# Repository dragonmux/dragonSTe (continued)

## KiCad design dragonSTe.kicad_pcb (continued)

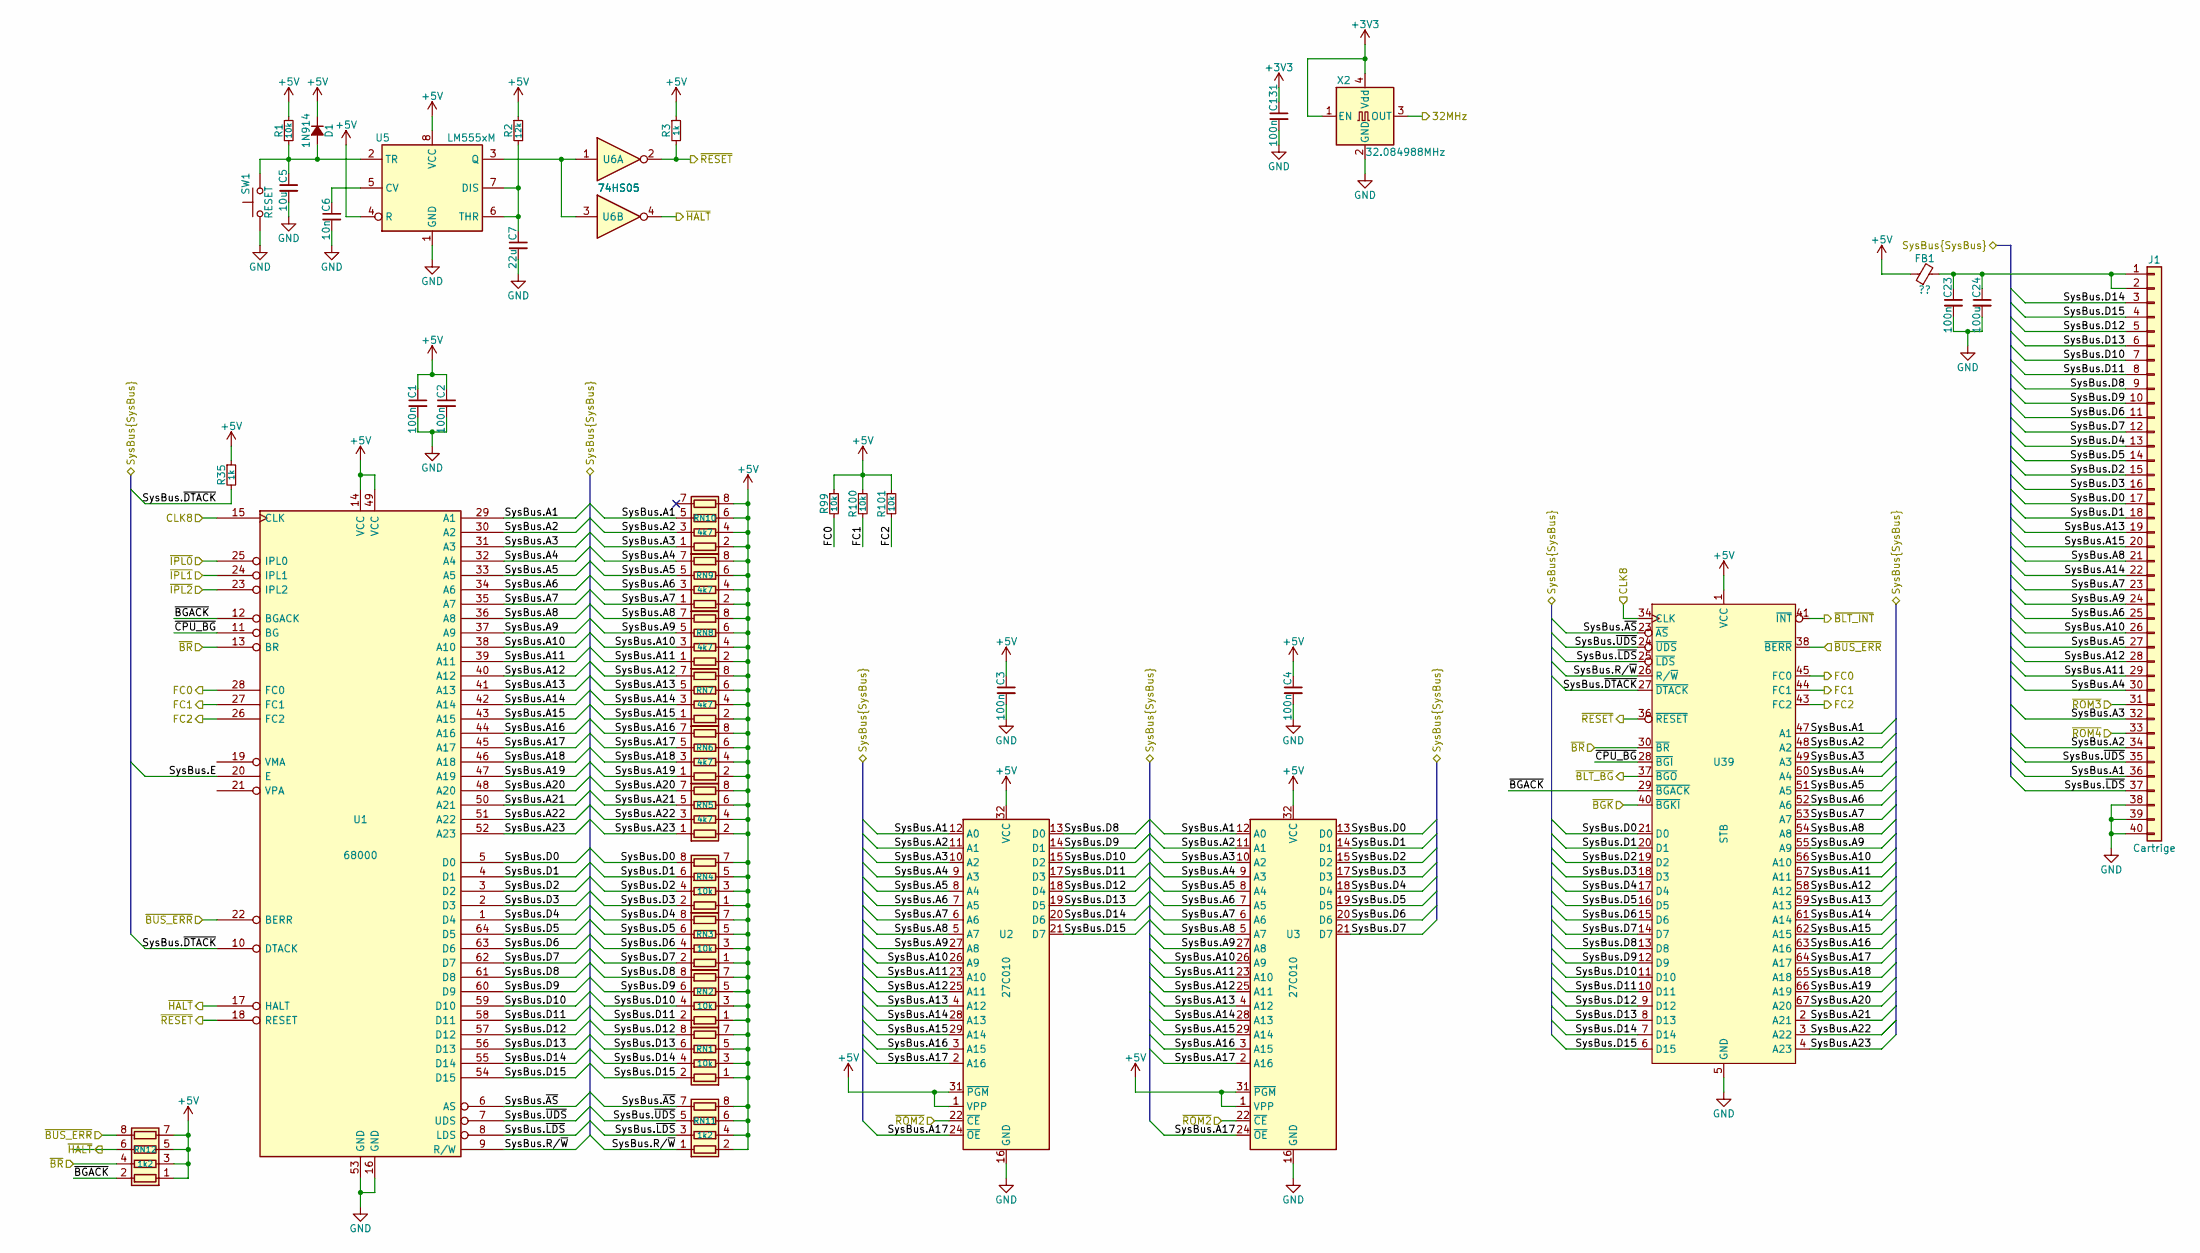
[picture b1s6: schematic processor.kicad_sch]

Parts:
C1, C2, C3, C4, C23, C131: 100n; C0603
C5: 10u; C0603
C6: 10n; C0603
C7: 22u; C0603
C24: 100u; C0603
D1: 1N914; D_SOD-323F; MPN 1N914BWS
FB1: ??
J1: Cartrige
R1, R99, R100, R101: 10k; R0603
R2: 12k; R0603
R3, R35: 1k; R0603
RN1, RN2, RN3, RN4: 10k; R0603_Array_Concave_4
RN5, RN6, RN7, RN8, RN9, RN10: 4k7; R0603_Array_Concave_4
RN11, RN12: 1k2; R0603_Array_Concave_4
SW1: RESET; B3U-1000P-B
U1: 68000; DIP-64_W22.86mm_Socket
U2, U3: 27C010; DIP-32_W15.24mm_Socket; MPN 4832-6000-CP
U5: LM555xM; SO-8_3.9x4.9mm_P1.27mm
U6: 74HS05; SO-14_3.9x8.65mm_P1.27mm; MPN SN74HC05DR
U39: STB; PLCC-68_SMD-Socket; MPN MC-68PLCC-SMT
X2: 32.084988MHz; SMD3225; MPN DSC8004CI2

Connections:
+3V3: C131.1, X2.1 (EN), X2.4 (Vdd); also elsewhere on the board
+5V: C1.1, C2.1, C3.1, C4.1, D1.1 (K), FB1.1, R1.1, R2.1, R3.1, R35.1, R99.1, R100.1, R101.1, RN1.1 (R1.1), RN1.3 (R3.1), RN1.5 (R4.2), RN1.7 (R2.2), RN2.1 (R1.1), RN2.3 (R3.1), RN2.5 (R4.2), RN2.7 (R2.2), RN3.1 (R1.1), RN3.3 (R3.1), RN3.5 (R4.2), RN3.7 (R2.2), RN4.1 (R1.1), RN4.3 (R3.1), RN4.5 (R4.2), RN4.7 (R2.2), RN5.2 (R2.1), RN5.4 (R4.1), RN5.6 (R3.2), RN5.8 (R1.2), RN6.2 (R2.1), RN6.4 (R4.1), RN6.6 (R3.2), RN6.8 (R1.2), RN7.2 (R2.1), RN7.4 (R4.1), RN7.6 (R3.2), RN7.8 (R1.2), RN8.2 (R2.1), RN8.4 (R4.1), RN8.6 (R3.2), RN8.8 (R1.2), RN9.2 (R2.1), RN9.4 (R4.1), RN9.6 (R3.2), RN9.8 (R1.2), RN10.2 (R2.1), RN10.4 (R4.1), RN10.6 (R3.2), RN10.8 (R1.2), RN11.2 (R2.1), RN11.4 (R4.1), RN11.6 (R3.2), RN11.8 (R1.2), RN12.1 (R1.1), RN12.3 (R3.1), RN12.5 (R4.2), RN12.7 (R2.2), U1.14 (VCC), U1.49 (VCC), U2.1 (VPP), U2.31 (~PGM), U2.32 (VCC), U3.1 (VPP), U3.31 (~PGM), U3.32 (VCC), U5.4 (R), U5.8 (VCC), U39.1 (VCC), U39.33 (VCC); also elsewhere on the board
/CPU+ROMs/32MHz: X2.3 (OUT); also elsewhere on the board
/CPU+ROMs/CLK8: U1.15 (CLK), U39.34 (CLK); also elsewhere on the board
/CPU+ROMs/FC0: R99.2, U1.28 (FC0), U39.45 (FC0); also elsewhere on the board
/CPU+ROMs/FC1: R100.2, U1.27 (FC1), U39.44 (FC1); also elsewhere on the board
/CPU+ROMs/FC2: R101.2, U1.26 (FC2), U39.43 (FC2); also elsewhere on the board
/CPU+ROMs/SysBus.A1: J1.36, RN10.5 (R4.2), U1.29 (A1), U2.12 (A0), U3.12 (A0), U39.47 (A1); also elsewhere on the board
/CPU+ROMs/SysBus.A2: J1.34, RN10.3 (R3.1), U1.30 (A2), U2.11 (A1), U3.11 (A1), U39.48 (A2); also elsewhere on the board
/CPU+ROMs/SysBus.A3: J1.32, RN10.1 (R1.1), U1.31 (A3), U2.10 (A2), U3.10 (A2), U39.49 (A3); also elsewhere on the board
/CPU+ROMs/SysBus.A4: J1.30, RN9.7 (R2.2), U1.32 (A4), U2.9 (A3), U3.9 (A3), U39.50 (A4); also elsewhere on the board
/CPU+ROMs/SysBus.A5: J1.27, RN9.5 (R4.2), U1.33 (A5), U2.8 (A4), U3.8 (A4), U39.51 (A5); also elsewhere on the board
/CPU+ROMs/SysBus.A6: J1.25, RN9.3 (R3.1), U1.34 (A6), U2.7 (A5), U3.7 (A5), U39.52 (A6); also elsewhere on the board
/CPU+ROMs/SysBus.A7: J1.23, RN9.1 (R1.1), U1.35 (A7), U2.6 (A6), U3.6 (A6), U39.53 (A7); also elsewhere on the board
/CPU+ROMs/SysBus.A8: J1.21, RN8.7 (R2.2), U1.36 (A8), U2.5 (A7), U3.5 (A7), U39.54 (A8); also elsewhere on the board
/CPU+ROMs/SysBus.A9: J1.24, RN8.5 (R4.2), U1.37 (A9), U2.27 (A8), U3.27 (A8), U39.55 (A9); also elsewhere on the board
/CPU+ROMs/SysBus.A10: J1.26, RN8.3 (R3.1), U1.38 (A10), U2.26 (A9), U3.26 (A9), U39.56 (A10); also elsewhere on the board
/CPU+ROMs/SysBus.A11: J1.29, RN8.1 (R1.1), U1.39 (A11), U2.23 (A10), U3.23 (A10), U39.57 (A11); also elsewhere on the board
/CPU+ROMs/SysBus.A12: J1.28, RN7.7 (R2.2), U1.40 (A12), U2.25 (A11), U3.25 (A11), U39.58 (A12); also elsewhere on the board
/CPU+ROMs/SysBus.A13: J1.19, RN7.5 (R4.2), U1.41 (A13), U2.4 (A12), U3.4 (A12), U39.59 (A13); also elsewhere on the board
/CPU+ROMs/SysBus.A14: J1.22, RN7.3 (R3.1), U1.42 (A14), U2.28 (A13), U3.28 (A13), U39.61 (A14); also elsewhere on the board
/CPU+ROMs/SysBus.A15: J1.20, RN7.1 (R1.1), U1.43 (A15), U2.29 (A14), U3.29 (A14), U39.62 (A15); also elsewhere on the board
/CPU+ROMs/SysBus.A16: RN6.7 (R2.2), U1.44 (A16), U2.3 (A15), U3.3 (A15), U39.63 (A16); also elsewhere on the board
/CPU+ROMs/SysBus.A17: RN6.5 (R4.2), U1.45 (A17), U2.2 (A16), U2.24 (~OE), U3.2 (A16), U3.24 (~OE), U39.64 (A17); also elsewhere on the board
/CPU+ROMs/SysBus.A18: RN6.3 (R3.1), U1.46 (A18), U39.65 (A18); also elsewhere on the board
/CPU+ROMs/SysBus.A19: RN6.1 (R1.1), U1.47 (A19), U39.66 (A19); also elsewhere on the board
/CPU+ROMs/SysBus.A20: RN5.7 (R2.2), U1.48 (A20), U39.67 (A20); also elsewhere on the board
/CPU+ROMs/SysBus.A21: RN5.5 (R4.2), U1.50 (A21), U39.2 (A21); also elsewhere on the board
/CPU+ROMs/SysBus.A22: RN5.3 (R3.1), U1.51 (A22), U39.3 (A22); also elsewhere on the board
/CPU+ROMs/SysBus.A23: RN5.1 (R1.1), U1.52 (A23), U39.4 (A23); also elsewhere on the board
/CPU+ROMs/SysBus.D0: J1.17, RN4.8 (R1.2), U1.5 (D0), U3.13 (D0), U39.21 (D0); also elsewhere on the board
/CPU+ROMs/SysBus.D1: J1.18, RN4.6 (R3.2), U1.4 (D1), U3.14 (D1), U39.20 (D1); also elsewhere on the board
/CPU+ROMs/SysBus.D2: J1.15, RN4.4 (R4.1), U1.3 (D2), U3.15 (D2), U39.19 (D2); also elsewhere on the board
/CPU+ROMs/SysBus.D3: J1.16, RN4.2 (R2.1), U1.2 (D3), U3.17 (D3), U39.18 (D3); also elsewhere on the board
/CPU+ROMs/SysBus.D4: J1.13, RN3.8 (R1.2), U1.1 (D4), U3.18 (D4), U39.17 (D4); also elsewhere on the board
/CPU+ROMs/SysBus.D5: J1.14, RN3.6 (R3.2), U1.64 (D5), U3.19 (D5), U39.16 (D5); also elsewhere on the board
/CPU+ROMs/SysBus.D6: J1.11, RN3.4 (R4.1), U1.63 (D6), U3.20 (D6), U39.15 (D6); also elsewhere on the board
/CPU+ROMs/SysBus.D7: J1.12, RN3.2 (R2.1), U1.62 (D7), U3.21 (D7), U39.14 (D7); also elsewhere on the board
/CPU+ROMs/SysBus.D8: J1.9, RN2.8 (R1.2), U1.61 (D8), U2.13 (D0), U39.13 (D8); also elsewhere on the board
/CPU+ROMs/SysBus.D9: J1.10, RN2.6 (R3.2), U1.60 (D9), U2.14 (D1), U39.12 (D9); also elsewhere on the board
/CPU+ROMs/SysBus.D10: J1.7, RN2.4 (R4.1), U1.59 (D10), U2.15 (D2), U39.11 (D10); also elsewhere on the board
/CPU+ROMs/SysBus.D11: J1.8, RN2.2 (R2.1), U1.58 (D11), U2.17 (D3), U39.10 (D11); also elsewhere on the board
/CPU+ROMs/SysBus.D12: J1.5, RN1.8 (R1.2), U1.57 (D12), U2.18 (D4), U39.9 (D12); also elsewhere on the board
/CPU+ROMs/SysBus.D13: J1.6, RN1.6 (R3.2), U1.56 (D13), U2.19 (D5), U39.8 (D13); also elsewhere on the board
/CPU+ROMs/SysBus.D14: J1.3, RN1.4 (R4.1), U1.55 (D14), U2.20 (D6), U39.7 (D14); also elsewhere on the board
/CPU+ROMs/SysBus.D15: J1.4, RN1.2 (R2.1), U1.54 (D15), U2.21 (D7), U39.6 (D15); also elsewhere on the board
/CPU+ROMs/SysBus.E: U1.20 (E); also elsewhere on the board
/CPU+ROMs/SysBus.R/~W: RN11.1 (R1.1), U1.9 (R/W), U39.26 (R/~W); also elsewhere on the board
/CPU+ROMs/SysBus.~AS: RN11.7 (R2.2), U1.6 (AS), U39.23 (~AS); also elsewhere on the board
/CPU+ROMs/SysBus.~DTACK: R35.2, U1.10 (DTACK), U39.27 (~DTACK); also elsewhere on the board
/CPU+ROMs/SysBus.~LDS: J1.37, RN11.3 (R3.1), U1.8 (LDS), U39.25 (~LDS); also elsewhere on the board
/CPU+ROMs/SysBus.~UDS: J1.35, RN11.5 (R4.2), U1.7 (UDS), U39.24 (~UDS); also elsewhere on the board
/CPU+ROMs/~BGACK: RN12.2 (R2.1), U1.12 (BGACK), U39.29 (~BGACK)
/CPU+ROMs/~BGK: U39.40 (~BGKI); also elsewhere on the board
/CPU+ROMs/~BLT_BG: U39.37 (~BGO); also elsewhere on the board
/CPU+ROMs/~BLT_INT: U39.41 (~INT); also elsewhere on the board
/CPU+ROMs/~BR: RN12.4 (R4.1), U1.13 (BR), U39.30 (~BR); also elsewhere on the board
/CPU+ROMs/~BUS_ERR: RN12.8 (R1.2), U1.22 (BERR), U39.38 (~BERR); also elsewhere on the board
/CPU+ROMs/~CPU_BG: U1.11 (BG), U39.28 (~BGI)
/CPU+ROMs/~HALT: RN12.6 (R3.2), U1.17 (HALT), U6.4
/CPU+ROMs/~IPL0: U1.25 (IPL0); also elsewhere on the board
/CPU+ROMs/~IPL1: U1.24 (IPL1); also elsewhere on the board
/CPU+ROMs/~IPL2: U1.23 (IPL2); also elsewhere on the board
/CPU+ROMs/~RESET: R3.2, U1.18 (RESET), U6.2, U39.36 (~RESET); also elsewhere on the board
/CPU+ROMs/~ROM2: U2.22 (~CE), U3.22 (~CE); also elsewhere on the board
GND: C1.2, C2.2, C3.2, C4.2, C5.2, C6.2, C7.2, C23.2, C24.2, C131.2, J1.38, J1.39, J1.40, SW1.1, U1.16 (GND), U1.53 (GND), U2.16 (GND), U3.16 (GND), U5.1 (GND), U39.5 (GND), U39.35 (GND), X2.2 (GND); also elsewhere on the board
unnamed: C5.1, D1.2 (A), R1.2, SW1.2, U5.2 (TR)
unnamed: C23.1, C24.1, FB1.2, J1.1, J1.2
unnamed: C6.1, U5.5 (CV)
unnamed: C7.1, R2.2, U5.6 (THR), U5.7 (DIS)
unnamed: U5.3 (Q), U6.1, U6.3

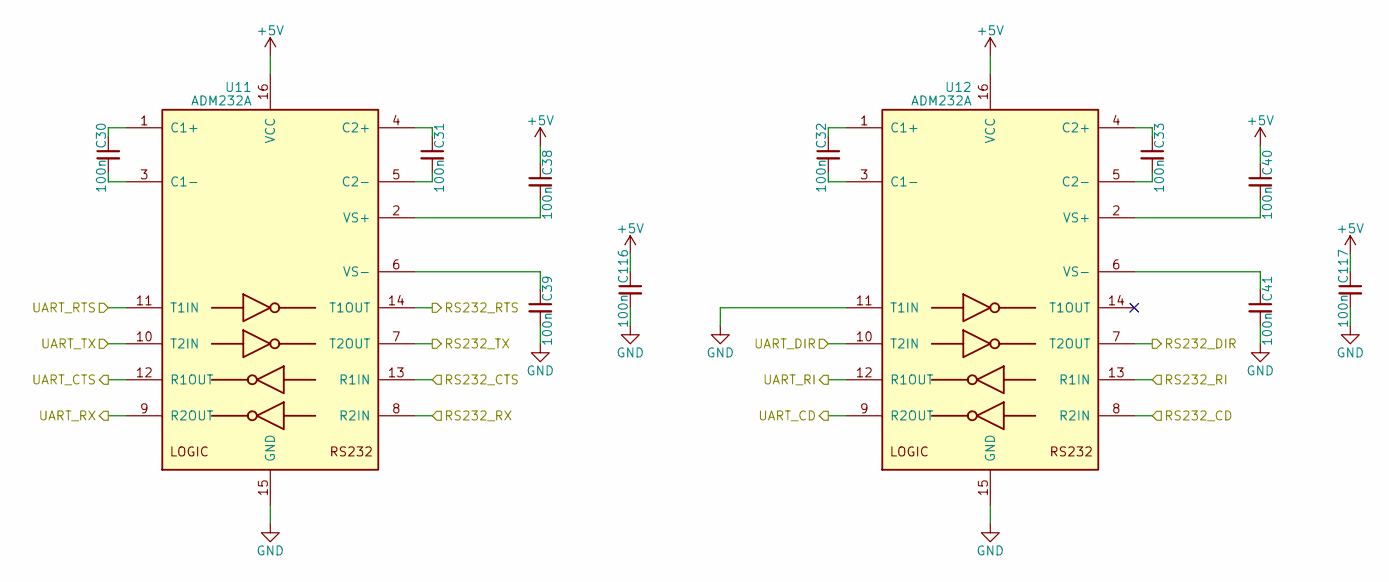
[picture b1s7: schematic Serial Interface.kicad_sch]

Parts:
C30, C31, C32, C33, C38, C39, C40, C41, C116, C117: 100n; C0603
U11, U12: ADM232A; SO-16_3.9x9.9mm_P1.27mm; MPN ADM232AARNZ-REEL7

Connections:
+5V: C38.1, C40.1, C116.1, C117.1, U11.16 (VCC), U12.16 (VCC); also elsewhere on the board
/IO Interfaces/Serial Interface/RS232_CD: U12.8 (R2IN); also elsewhere on the board
/IO Interfaces/Serial Interface/RS232_CTS: U11.13 (R1IN); also elsewhere on the board
/IO Interfaces/Serial Interface/RS232_DIR: U12.7 (T2OUT); also elsewhere on the board
/IO Interfaces/Serial Interface/RS232_RI: U12.13 (R1IN); also elsewhere on the board
/IO Interfaces/Serial Interface/RS232_RTS: U11.14 (T1OUT); also elsewhere on the board
/IO Interfaces/Serial Interface/RS232_RX: U11.8 (R2IN); also elsewhere on the board
/IO Interfaces/Serial Interface/RS232_TX: U11.7 (T2OUT); also elsewhere on the board
/IO Interfaces/Serial Interface/UART_CD: U12.9 (R2OUT); also elsewhere on the board
/IO Interfaces/Serial Interface/UART_CTS: U11.12 (R1OUT); also elsewhere on the board
/IO Interfaces/Serial Interface/UART_DIR: U12.10 (T2IN); also elsewhere on the board
/IO Interfaces/Serial Interface/UART_RI: U12.12 (R1OUT); also elsewhere on the board
/IO Interfaces/Serial Interface/UART_RTS: U11.11 (T1IN); also elsewhere on the board
/IO Interfaces/Serial Interface/UART_RX: U11.9 (R2OUT); also elsewhere on the board
/IO Interfaces/Serial Interface/UART_TX: U11.10 (T2IN); also elsewhere on the board
GND: C39.2, C41.2, C116.2, C117.2, U11.15 (GND), U12.11 (T1IN), U12.15 (GND); also elsewhere on the board
unnamed: C30.1, U11.1 (C1+)
unnamed: C30.2, U11.3 (C1-)
unnamed: C31.1, U11.4 (C2+)
unnamed: C31.2, U11.5 (C2-)
unnamed: C38.2, U11.2 (VS+)
unnamed: C39.1, U11.6 (VS-)
unnamed: C32.1, U12.1 (C1+)
unnamed: C32.2, U12.3 (C1-)
unnamed: C33.1, U12.4 (C2+)
unnamed: C33.2, U12.5 (C2-)
unnamed: C40.2, U12.2 (VS+)
unnamed: C41.1, U12.6 (VS-)

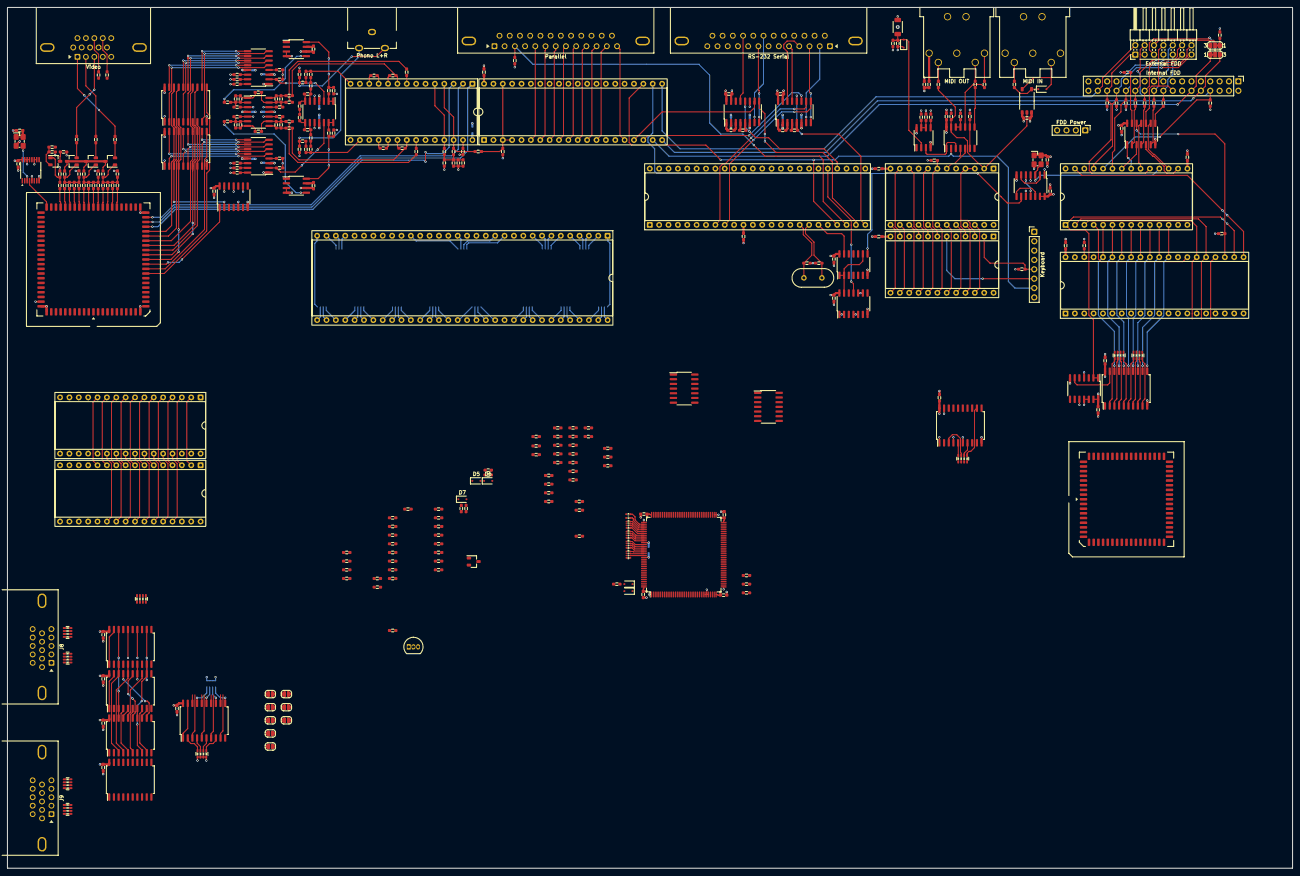
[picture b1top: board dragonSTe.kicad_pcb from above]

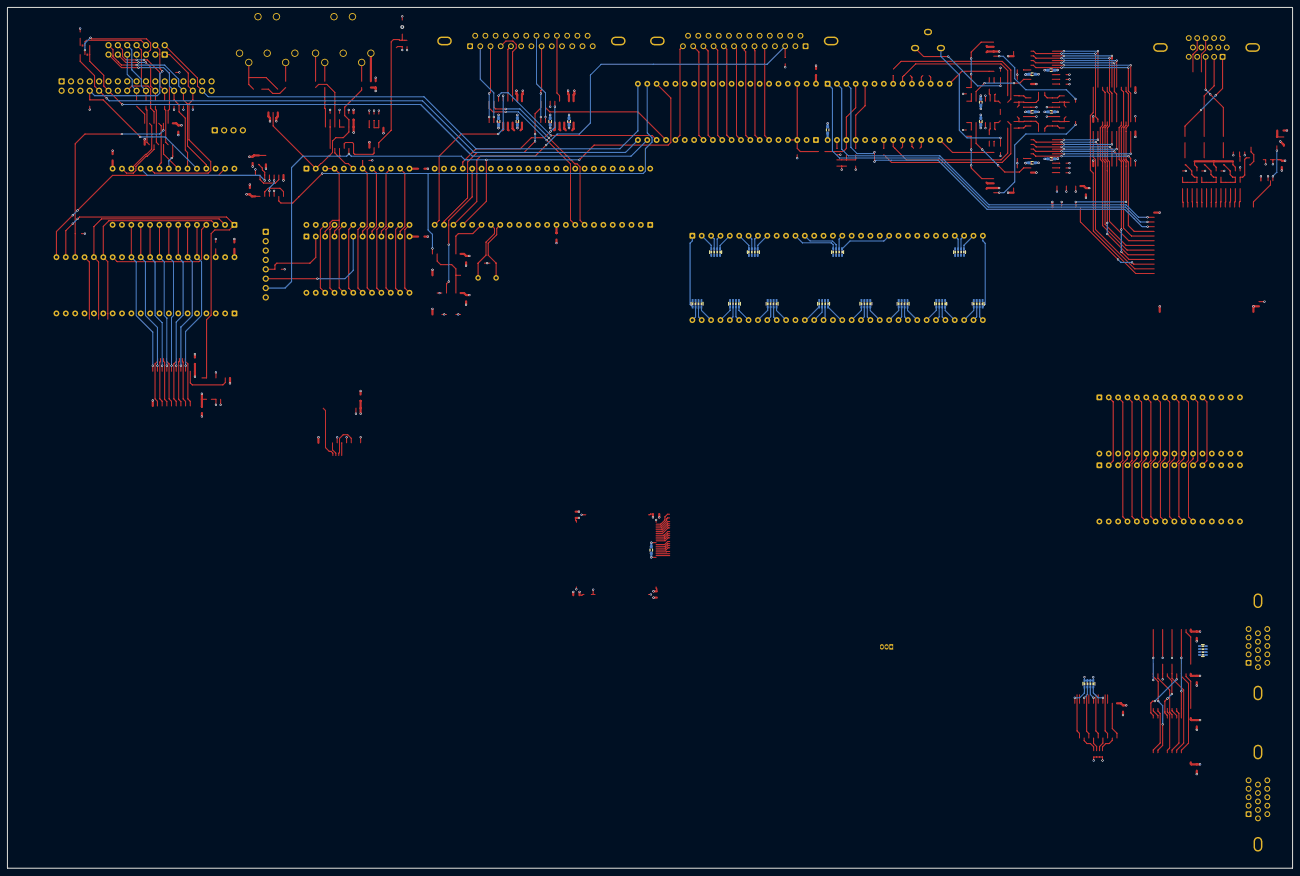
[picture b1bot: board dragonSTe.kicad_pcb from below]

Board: 4 copper layers, 348.3 x 233.3 mm, 341 parts (28 on the bottom side), 409 nets.

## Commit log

2025-05-12 motherboard: Created a KiCad project and sane Git ignores for this project
2025-05-12 motherboard: Added a schematic that captures the bulk of the processor and ROMs page of the STe
2025-05-12 motherboard: Added a schematic that captures most of the DAC/sound and joysticks page of the STe
2025-05-12 motherboard: Added a schematic that captures the bulk of the serial and parallel I/O interfaces page of the STe
2025-05-12 motherboard: Added a schematic that captures the start of the floppy and HDD page of the STe
2025-05-12 motherboard: Added a schematic page that captures the overarchching connections of the STe and an initial PCB file
2025-05-12 motherboard: Added the circuitry for the joystick pads
2025-05-13 motherboard: Created a suite of custom symbols for board-specific parts
2025-05-13 motherboard: Added the HDD and FDD controller logic to the schematic
2025-05-13 motherboard: Created a symbol for the BLiTTER chip
2025-05-13 motherboard: Added the BLiTTER to the schematic and tidied up a pile
2025-05-14 motherboard: Added a schematic symbol for the GST MCU
2025-05-14 motherboard: Added SHIFTER to the schematic and tidied up a pile
2025-05-15 motherboard: Begun building the schematic chunk for the SIM slots
2025-05-15 motherboard: Schematic cleanup in the peripherals sections
2025-05-15 motherboard: Further filled out the schematic for the video interface
2025-05-15 motherboard: Worked on fleshing out more of the top-level schematic, filling in more of the connections that need to be made between blocks
2025-05-15 motherboard: More signal routing, and starting in on the BoM
2025-05-15 motherboard: Begun routing the internal floppy disk interface
2025-05-15 motherboard: Begun routing the FM synth sound chip
2025-05-15 motherboard: Routed one of the parallel interfaces and the ROMs
2025-05-16 motherboard: Fixed the floppy power connector and defined the board parameters for manufacture
2025-05-17 motherboard: Fixed a pile of resistor network issues, and concluded initial routing of the CPU and audio amp passives
2025-05-18 motherboard: Added packaging and ordering information for many of the 7400 logic parts and the DACs
2025-05-18 motherboard: Routed out the bulk of the DAC section and feed latches
2025-05-18 motherboard: Routing for the joystick ports
2025-05-19 motherboard: Added a note about how the FCLK signal works and how the Butterworth filter cutoffs work
2025-05-20 motherboard: Added the Butterworth filters for the audio paths so they work correctly
2025-05-23 motherboard: Added the main RCA-based audio out connections, completing the audio section
2025-05-23 motherboard: Reorganised a bit to start bringing the I/O interfaces together and setting their routing into place a bit
2025-05-24 motherboard: Added more footprints for parts and refined the serial comms section further
2025-05-24 motherboard: Placed and routed the RS-232 front-end and some of the control logic and parts for the MFP
2025-05-25 motherboard: Added the external keyboard connector and put the FDD interface into probably its final resting spot
2025-05-25 motherboard: Routed in the external floppy interface connector
2025-05-25 motherboard: Corrected the connectors used for the 25-pin interfaces and set their part numbers
2025-05-25 motherboard: Mostly routed the ~button signal circuitry
2025-05-25 motherboard: Sorted out a portion of the HDD interface
2025-05-26 motherboard: Sorted some of the clock generation circuitry out
2025-05-27 motherboard: Sorted out the secondary clock source
2025-05-27 motherboard: Completed the MIDI in interface having identified the component PC-900 from the original schematic
2025-05-27 motherboard: Sorted out all the 1N914's having found a suitable part
2025-05-27 motherboard: Routed in the CLK2 and SCLK signals
2025-05-27 motherboard: Initial placement and routing of the 1N914 diodes
2025-05-28 motherboard: Sorted out the connectors for the joystick ports and video port
2025-05-28 motherboard: Placed the video output and SHIFTER
2025-05-28 motherboard: Routed in the sound DMA output and microwire control from SHIFTER
2025-05-29 motherboard: Cleaned up the clock tree implementation, specifying and fixing down how to do the 32MHz clock source
2025-05-29 motherboard: Fixed a missing connection in the HDD interface drive circuitry
2025-05-29 motherboard: Cleaned up the board with the new changes, and routed in the HDD interface data buffer
2025-05-29 motherboard: Plumbed in MCLK to the mux and SHIFTER
2025-05-29 motherboard: Routed the video output from SHIFTER
2025-05-29 motherboard: Cleaned up the board layout and outline
2025-05-29 motherboard: Routed in the last of the HDD control buffers, and begun routing in BLiTTER
